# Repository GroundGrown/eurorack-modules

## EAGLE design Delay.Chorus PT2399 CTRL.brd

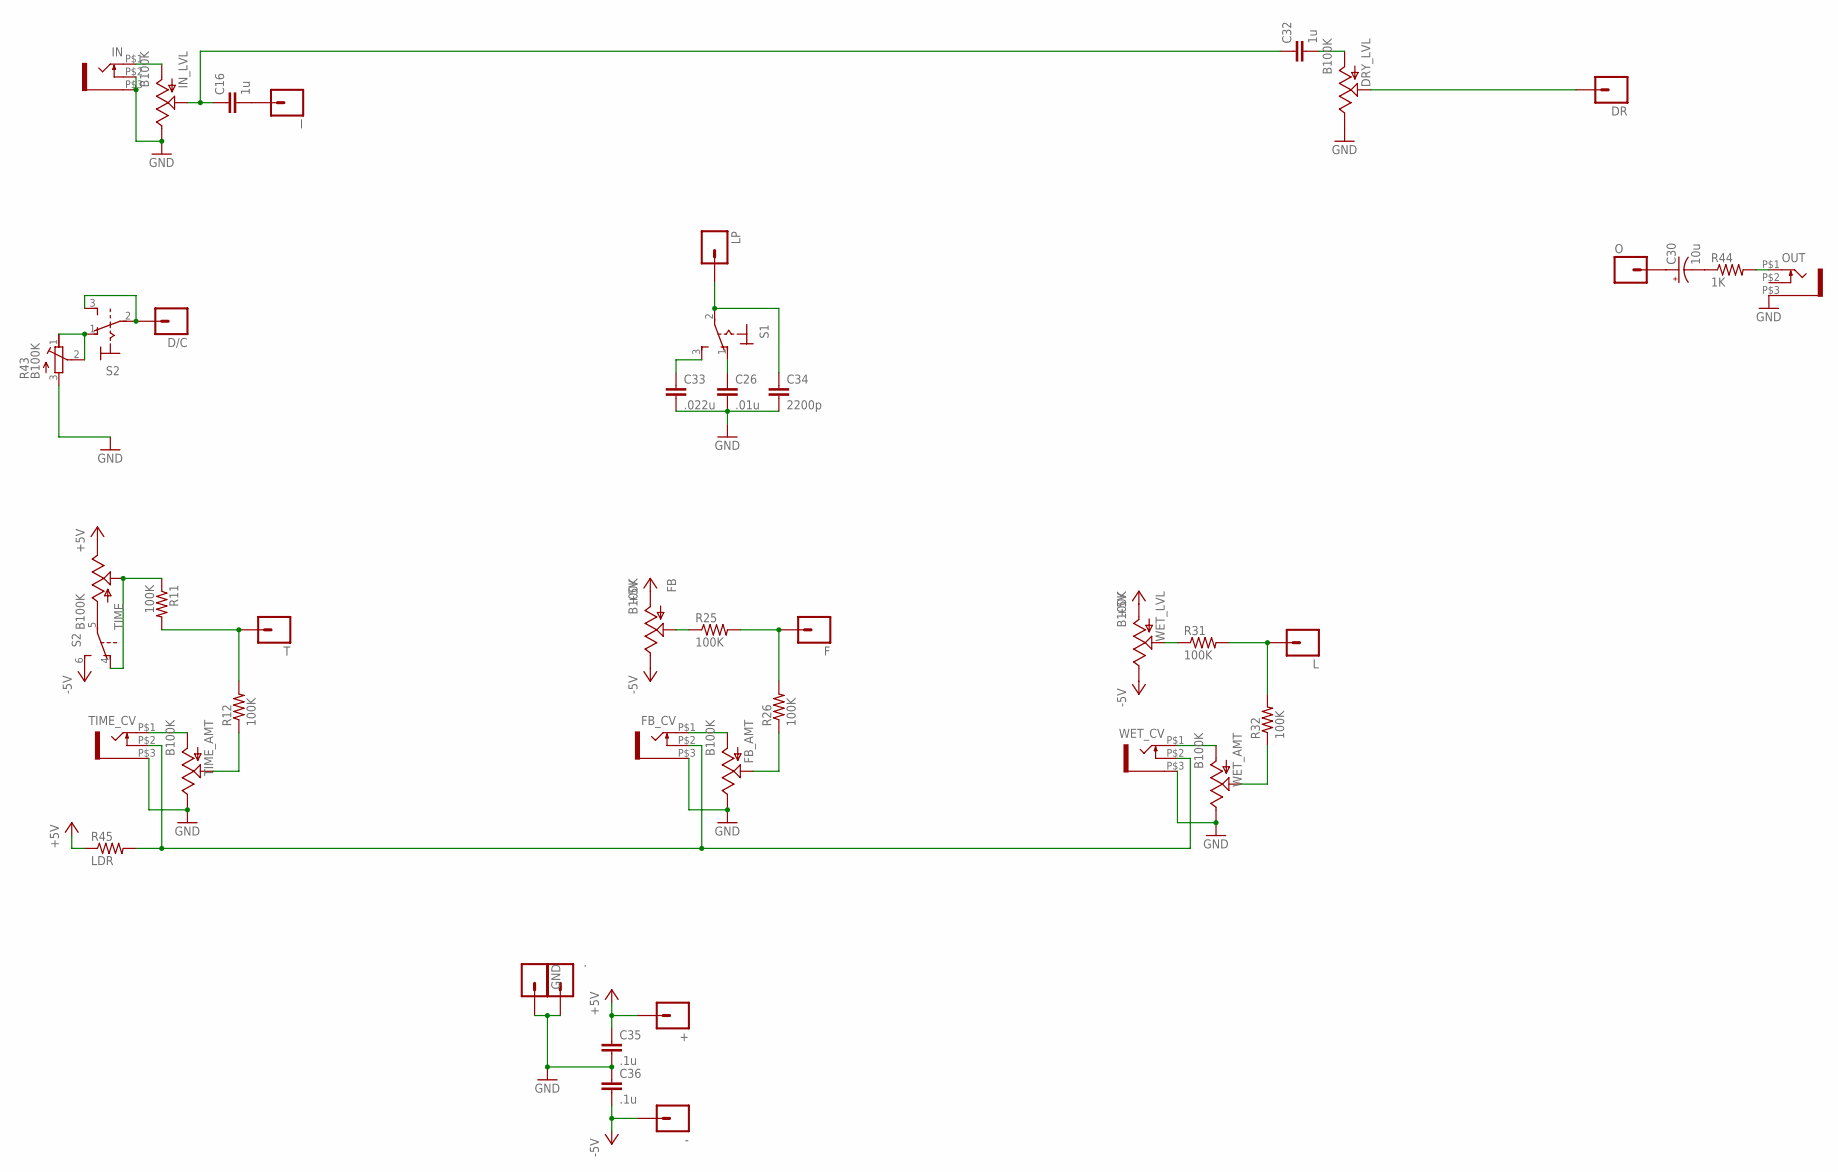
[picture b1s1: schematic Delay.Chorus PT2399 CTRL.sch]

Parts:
+: M01PTH; 1X01
-: M01PTH; 1X01
.: M01PTH; 1X01
C16, C32: 1u; 1206
C26: .01u; C5B2.5
C30: 10u; CPOL-RADIAL-10UF-25V
C33: .022u; C5B2.5
C34: 2200p; C5B2.5
C35, C36: .1u; 0805
D/C: M01PTH; 1X01
DR: M01PTH; 1X01
DRY_LVL: B100K; ALPS_POT
F: M01PTH; 1X01
FB: B100K; ALPS_POT
FB_AMT: B100K; ALPS_POT
FB_CV: WQP-PJ301M-12_JACK
GND: M01PTH; 1X01
I: M01PTH; 1X01
IN: WQP-PJ301M-12_JACK
IN_LVL: B100K; ALPS_POT
L: M01PTH; 1X01
LP: M01PTH; 1X01
O: M01PTH; 1X01
OUT: WQP-PJ301M-12_JACK
R11, R12, R25, R26, R31, R32: 100K; 0805
R43: B100K; RTRIM3314G
R44: 1K; 0805
R45: LDR; 1/6W-RES
S1: M9040P
S2: M9040P2
T: M01PTH; 1X01
TIME: B100K; ALPS_POT
TIME_AMT: B100K; ALPS_POT
TIME_CV: WQP-PJ301M-12_JACK
WET_AMT: B100K; ALPS_POT
WET_CV: WQP-PJ301M-12_JACK
WET_LVL: B100K; ALPS_POT

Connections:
+5V: +.1, C35.1, FB.P$3 (A), R45.1, TIME.P$1 (E), WET_LVL.P$3 (A)
-5V: -.1, C36.2, FB.P$1 (E), S2.6 (S), WET_LVL.P$1 (E)
GND: ..1, C26.2, C33.2, C34.2, C35.2, C36.1, DRY_LVL.P$1 (E), FB_AMT.P$1 (E), FB_CV.P$3 (1), GND.1, IN.P$2 (3), IN.P$3 (1), IN_LVL.P$1 (E), OUT.P$3 (1), R43.3 (A), TIME_AMT.P$1 (E), TIME_CV.P$3 (1), WET_AMT.P$1 (E), WET_CV.P$3 (1)
unnamed: D/C.1, S2.2, S2.3 (S)
unnamed: DR.1, DRY_LVL.P$2 (S)
unnamed: C30.1 (+), O.1
unnamed: S2.5, TIME.P$3 (A)
unnamed: C30.2 (-), R44.1
unnamed: OUT.P$1 (2), R44.2
unnamed: IN.P$1 (2), IN_LVL.P$3 (A)
unnamed: C16.1, C32.1, IN_LVL.P$2 (S)
unnamed: C16.2, I.1
unnamed: TIME_AMT.P$3 (A), TIME_CV.P$1 (2)
unnamed: R12.1, TIME_AMT.P$2 (S)
unnamed: R11.1, S2.4 (O), TIME.P$2 (S)
unnamed: R11.2, R12.2, T.1
unnamed: FB_AMT.P$3 (A), FB_CV.P$1 (2)
unnamed: FB_AMT.P$2 (S), R26.1
unnamed: FB.P$2 (S), R25.1
unnamed: F.1, R25.2, R26.2
unnamed: WET_AMT.P$3 (A), WET_CV.P$1 (2)
unnamed: R32.1, WET_AMT.P$2 (S)
unnamed: R31.1, WET_LVL.P$2 (S)
unnamed: L.1, R31.2, R32.2
unnamed: C32.2, DRY_LVL.P$3 (A)
unnamed: C26.1, S1.1 (O)
unnamed: C33.1, S1.3 (S)
unnamed: C34.1, LP.1, S1.2
unnamed: R43.1 (E), R43.2 (S), S2.1 (O)
unnamed: FB_CV.P$2 (3), R45.2, TIME_CV.P$2 (3), WET_CV.P$2 (3)

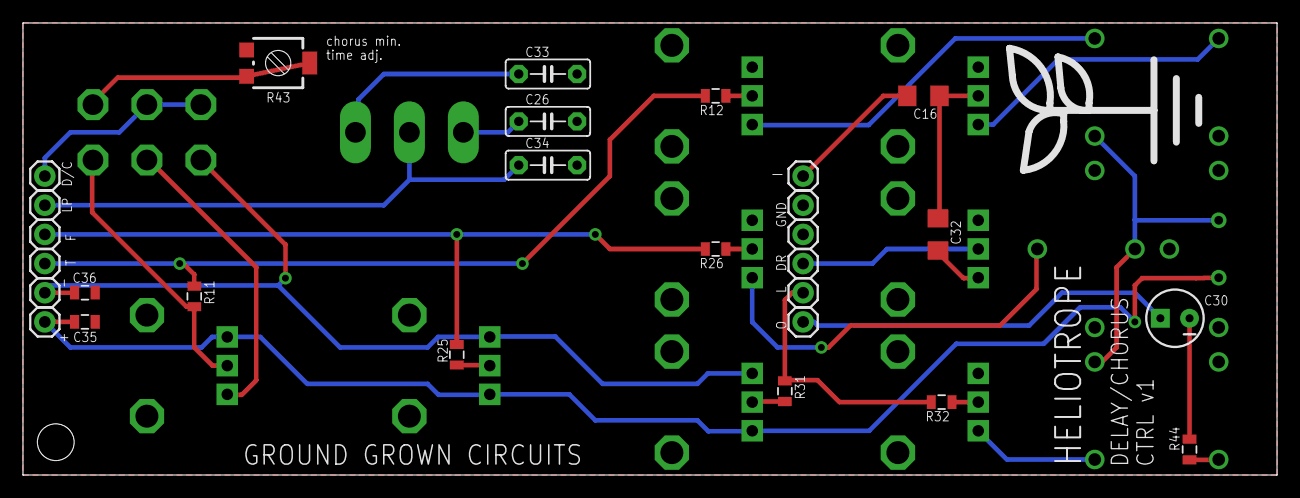
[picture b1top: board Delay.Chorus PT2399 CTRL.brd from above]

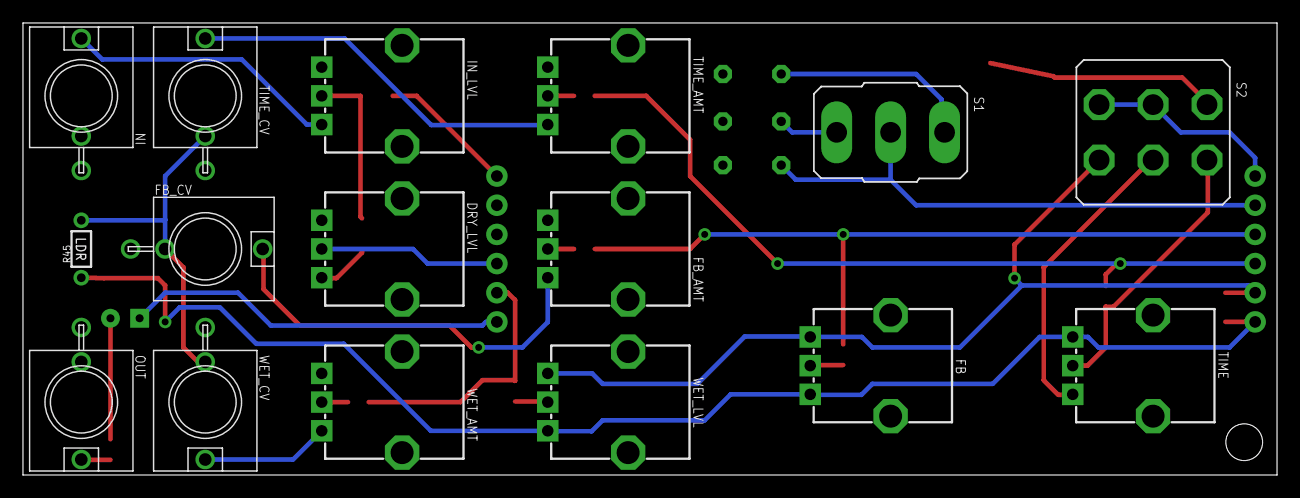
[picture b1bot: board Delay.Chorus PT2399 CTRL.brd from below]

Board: 2 copper layers, 109.2 x 39.4 mm, 45 parts (16 on the bottom side), 30 nets.

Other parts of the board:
U$1: LOGO_LARGE

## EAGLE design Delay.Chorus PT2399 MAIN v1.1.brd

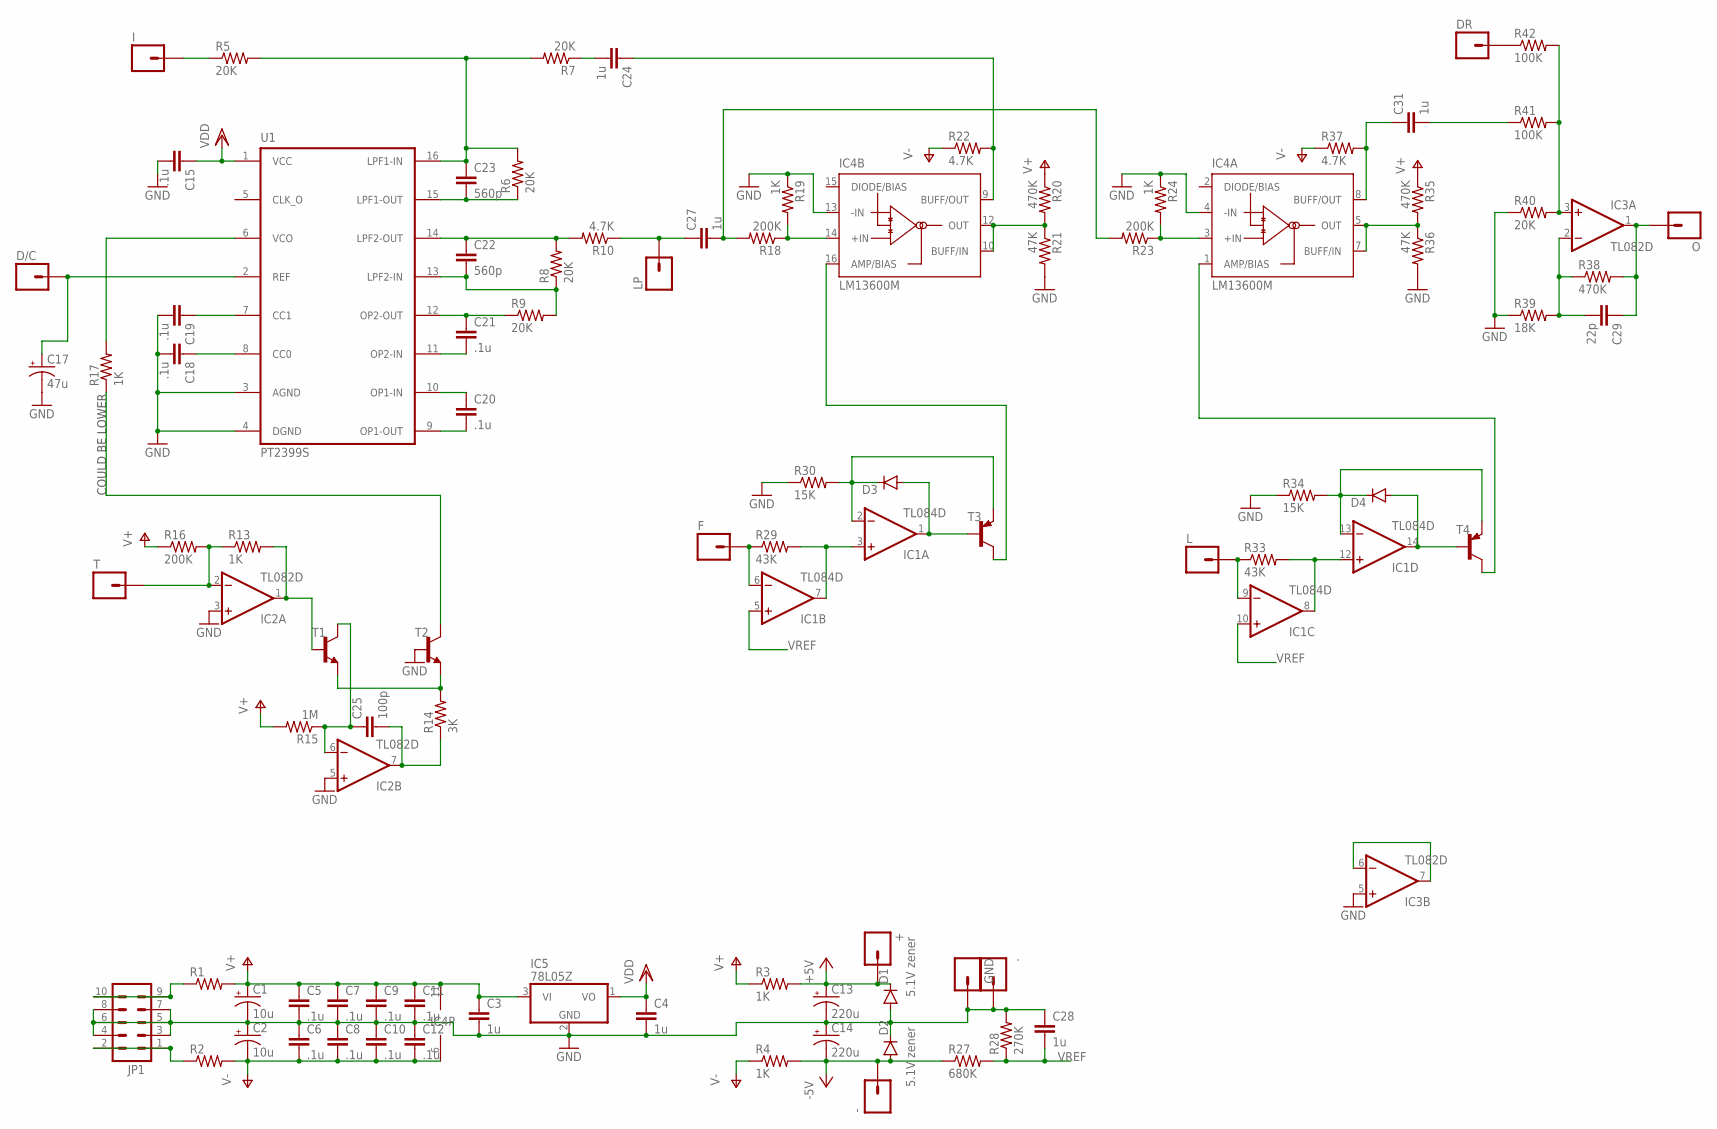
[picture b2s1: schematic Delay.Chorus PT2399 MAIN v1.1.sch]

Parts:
+: M01PTH; 1X01
-: M01PTH; 1X01
.: M01PTH; 1X01
C1, C2: 10u; CPOL-RADIAL-10UF-25V
C3, C4, C24, C27, C28, C31: 1u; 0805
C5, C6, C7, C8, C9, C10, C11, C12, C15, C18, C19, C20, C21: .1u; 0805
C13, C14: 220u; E2,5-5
C17: 47u; E2,5-5
C22, C23: 560p; 0805
C25: 100p; 0805
C29: 22p; 0805
D1, D2: 5.1V zener; SOD-123
D3, D4: DIODESOD123; SOD-123
D/C: M01PTH; 1X01
DR: M01PTH; 1X01
F: M01PTH; 1X01
GND: M01PTH; 1X01
I: M01PTH; 1X01
IC1: TL084D; SO14
IC2, IC3: TL082D; SO08
IC4: LM13600M; SO16
IC5: 78L05Z; TO92
JP1: M05X2PTH; AVR_ICSP
L: M01PTH; 1X01
LP: M01PTH; 1X01
O: M01PTH; 1X01
R1, R2: RESISTOR0805-RES; 0805
R3, R4, R13, R17, R19, R24: 1K; 0805
R5, R6, R7, R8, R9, R40: 20K; 0805
R10, R22, R37: 4.7K; 0805
R14: 3K; 0805
R15: 1M; 0805
R16, R18, R23: 200K; 0805
R20, R35, R38: 470K; 0805
R21, R36: 47K; 0805
R27: 680K; 0805
R28: 270K; 0805
R29, R33: 43K; 0805
R30, R34: 15K; 0805
R39: 18K; 0805
R41, R42: 100K; 0805
T: M01PTH; 1X01
T1, T2: MMBT3904LT1-NPN-SOT23-BEC; SOT23-BEC
T3, T4: MMBT3906LT1-PNP-SOT23-BEC; SOT23-BEC
U1: PT2399S; SO16W

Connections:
+5V: +.1, C13.+, D1.C, R3.2
-5V: -.1, C14.-, D2.A, R4.2, R27.1
GND: ..1, C1.2 (-), C2.1 (+), C3.2, C4.2, C5.2, C6.1, C7.2, C8.1, C9.2, C10.1, C11.2, C12.1, C13.-, C14.+, C15.2, C17.-, C18.2, C19.2, C28.1, D1.A, D2.C, GND.1, IC2.3 (+IN), IC2.5 (+IN), IC3.5 (+IN), IC4.4 (-IN), IC4.13 (-IN), IC5.2 (GND), JP1.3, JP1.4, JP1.5, JP1.6, JP1.7, JP1.8, R19.1, R21.2, R24.1, R28.2, R30.1, R34.1, R36.2, R39.1, R40.1, T2.B, U1.3 (AGND), U1.4 (DGND)
unnamed: C17.+, D/C.1, U1.2 (REF)
unnamed: C19.1, U1.7 (CC1)
unnamed: C18.1, U1.8 (CC0)
unnamed: C23.1, R5.2, R6.2, R7.2, U1.16 (LPF1-IN)
unnamed: C22.1, R8.2, R10.2, U1.14 (LPF2-OUT)
unnamed: C22.2, R8.1, R9.2, U1.13 (LPF2-IN)
unnamed: C21.1, R9.1, U1.12 (OP2-OUT)
unnamed: C21.2, U1.11 (OP2-IN)
unnamed: JP1.1, JP1.2, R2.1
unnamed: JP1.9, JP1.10, R1.1
unnamed: C20.1, U1.10 (OP1-IN)
unnamed: C20.2, U1.9 (OP1-OUT)
unnamed: C23.2, R6.1, U1.15 (LPF1-OUT)
unnamed: DR.1, R42.1
unnamed: I.1, R5.1
unnamed: C24.2, R7.1
unnamed: C24.1, IC4.9 (BUFF/OUT), R22.2
unnamed: F.1, IC1.6 (-IN), R29.1
unnamed: IC2.2 (-IN), R13.1, R16.2, T.1
unnamed: IC2.1 (OUT), R13.2, T1.B
unnamed: R14.2, T1.E, T2.E
unnamed: C25.2, IC2.7 (OUT), R14.1
unnamed: C25.1, IC2.6 (-IN), R15.1, T1.C
unnamed: C27.2, R18.2, R23.2
unnamed: R17.1, T2.C
unnamed: R17.2, U1.6 (VCO)
unnamed: IC4.14 (+IN), R18.1, R19.2
unnamed: IC4.10 (BUFF/IN), IC4.12 (OUT), R20.2, R21.1
unnamed: IC4.3 (+IN), R23.1, R24.2
unnamed: IC1.3 (+IN), IC1.7 (OUT), R29.2
unnamed: D3.C, IC1.2 (-IN), R30.2, T3.E
unnamed: D3.A, IC1.1 (OUT), T3.B
unnamed: IC4.5 (OUT), IC4.7 (BUFF/IN), R35.2, R36.1
unnamed: IC4.16 (AMP/BIAS), T3.C
unnamed: IC1.8 (OUT), IC1.12 (+IN), R33.2
unnamed: D4.C, IC1.13 (-IN), R34.2, T4.E
unnamed: D4.A, IC1.14 (OUT), T4.B
unnamed: IC4.1 (AMP/BIAS), T4.C
unnamed: C31.1, IC4.8 (BUFF/OUT), R37.2
unnamed: C29.2, IC3.2 (-IN), R38.1, R39.2
unnamed: C29.1, IC3.1 (OUT), O.1, R38.2
unnamed: IC1.9 (-IN), L.1, R33.1
unnamed: IC3.3 (+IN), R40.2, R41.2, R42.2
unnamed: C31.2, R41.1
unnamed: IC3.6 (-IN), IC3.7 (OUT)
unnamed: C27.1, LP.1, R10.1
V+: C1.1 (+), C3.1, C5.1, C7.1, C9.1, C11.1, IC1.4 (V+), IC2.8 (V+), IC3.8 (V+), IC4.11 (V+), IC5.3 (VI), R1.2, R3.1, R15.2, R16.1, R20.1, R35.1
V-: C2.2 (-), C6.2, C8.2, C10.2, C12.2, IC1.11 (V-), IC2.4 (V-), IC3.4 (V-), IC4.6 (V-), R2.2, R4.1, R22.1, R37.1
VDD: C4.1, C15.1, IC5.1 (VO), U1.1 (VCC)
VREF: C28.2, IC1.5 (+IN), IC1.10 (+IN), R27.2, R28.1

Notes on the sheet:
COULD BE LOWER

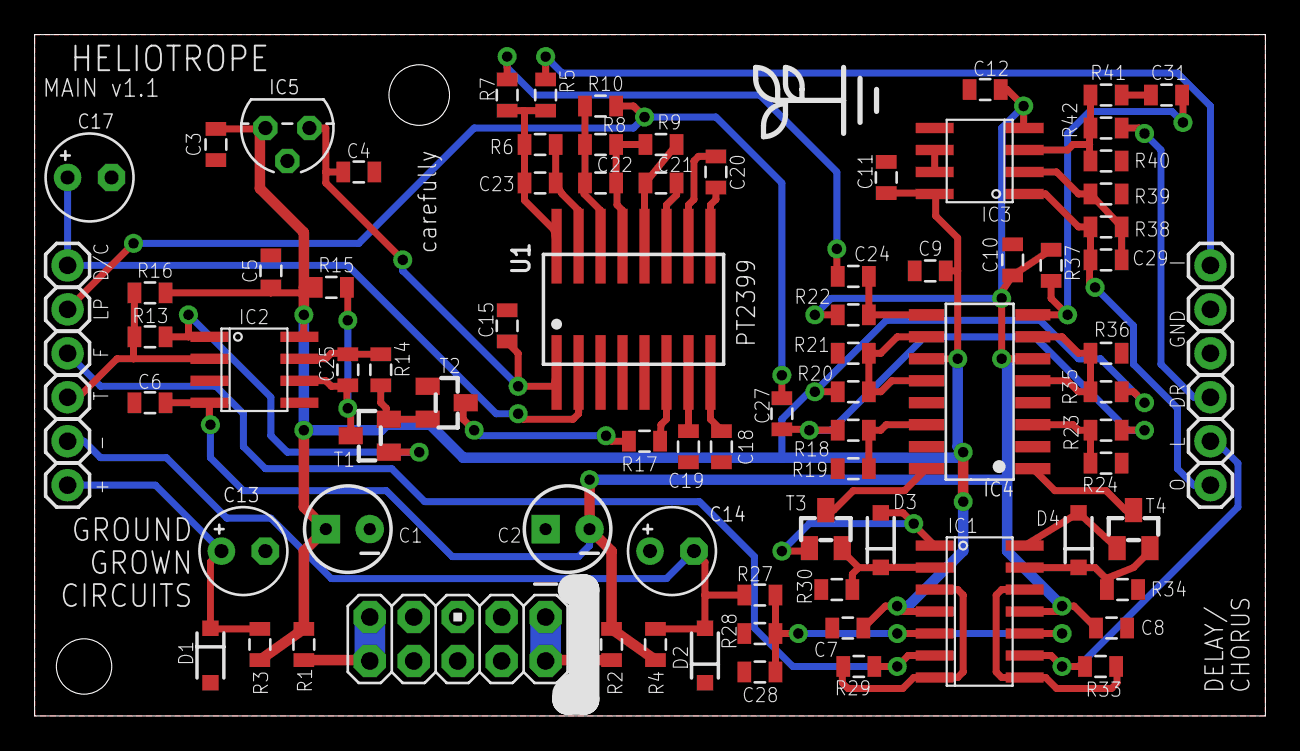
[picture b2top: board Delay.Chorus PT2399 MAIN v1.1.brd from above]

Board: 2 copper layers, 71.1 x 39.4 mm, 92 parts (0 on the bottom side), 53 nets.

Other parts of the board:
U$1: LOGO_SMALL

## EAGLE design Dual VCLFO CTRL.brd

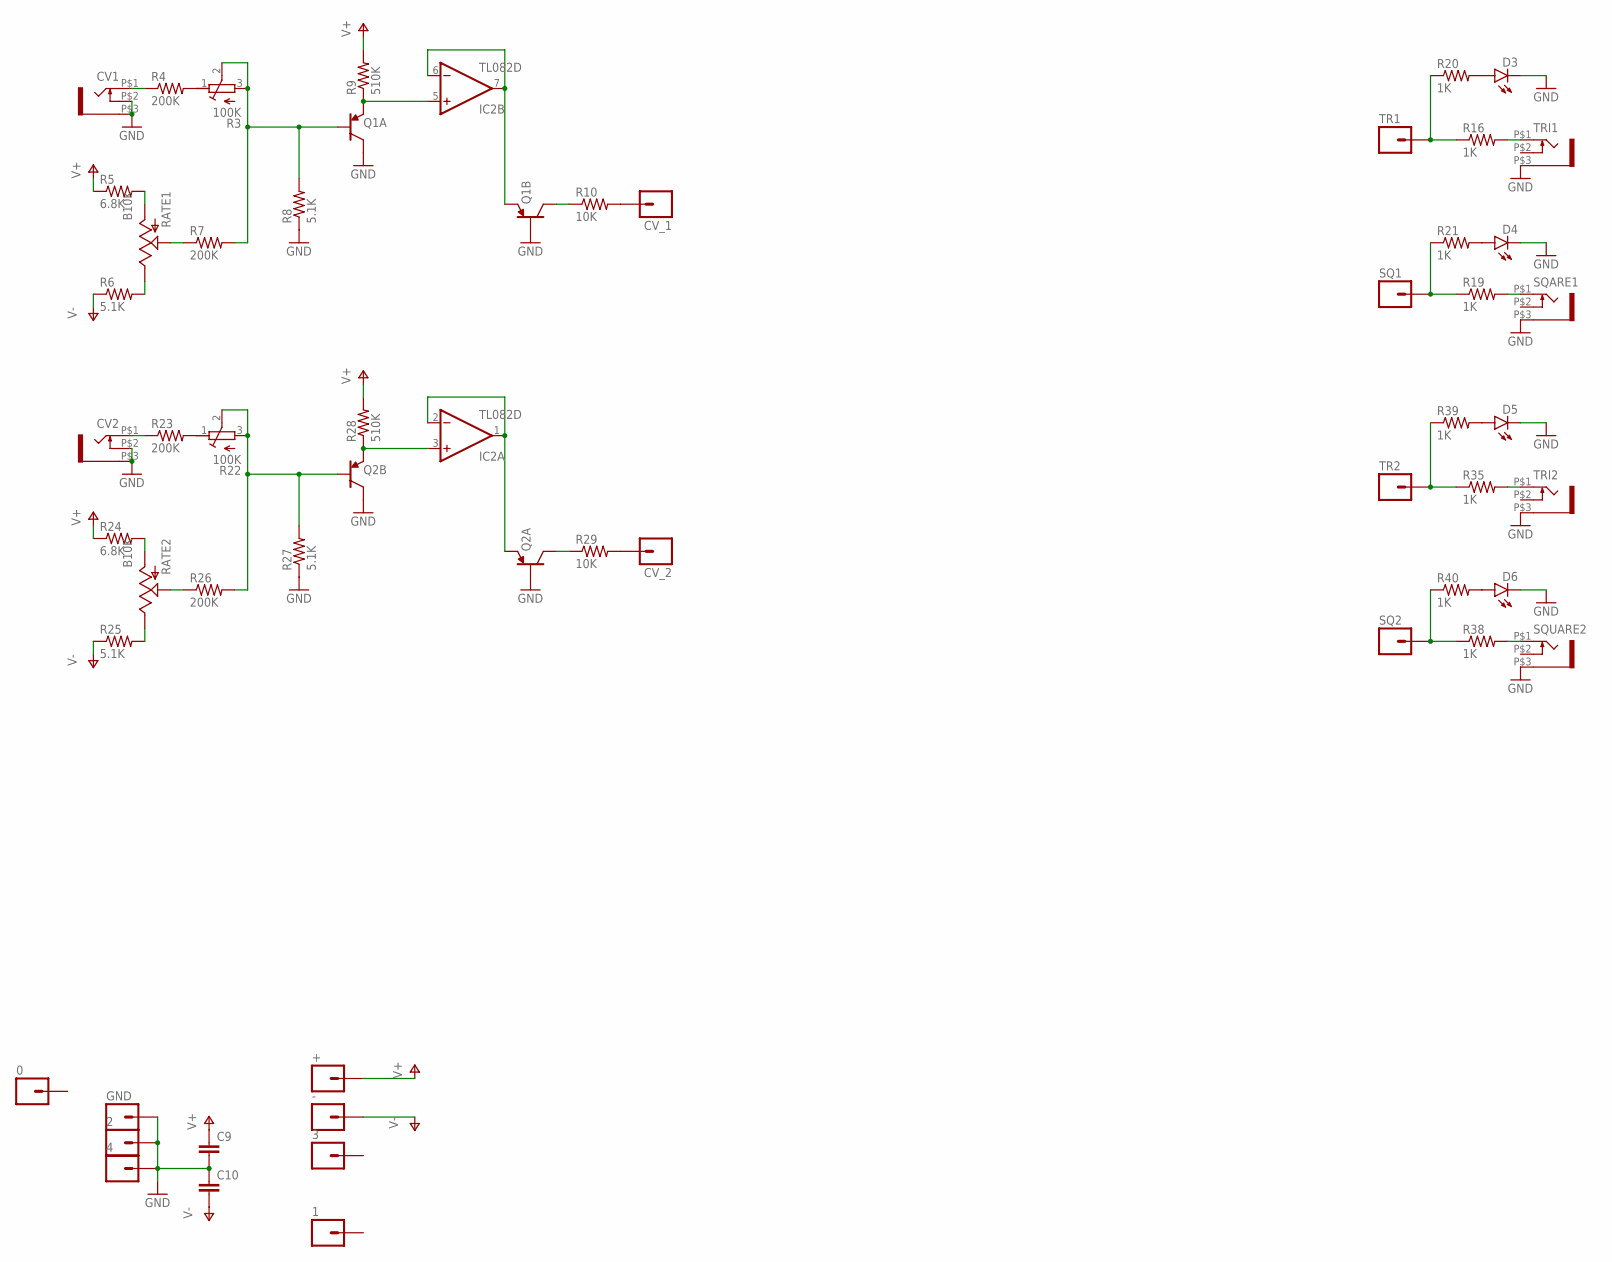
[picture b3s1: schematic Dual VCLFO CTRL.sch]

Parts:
0, 1, 2, 3, 4: M01PTH; 1X01
+: M01PTH; 1X01
-: M01PTH; 1X01
C9, C10: CAP0805; 0805
CV1, CV2: WQP-PJ301M-12_JACK
CV_1, CV_2: M01PTH; 1X01
D3, D4, D5, D6: LED3MM
GND: M01PTH; 1X01
IC2: TL082D; SO08
Q1, Q2: PNP-DUALPMP5201; SOT363
R3, R22: 100K; RTRIM3314G
R4, R7, R23, R26: 200K; 0805
R5, R24: 6.8K; 0805
R6, R8, R25, R27: 5.1K; 0805
R9, R28: 510K; 0805
R10, R29: 10K; 0805
R16, R19, R20, R21, R35, R38, R39, R40: 1K; 0805
RATE1, RATE2: B10K; ALPS_POT
SQ1, SQ2: M01PTH; 1X01
SQARE1: WQP-PJ301M-12_JACK
SQUARE2: WQP-PJ301M-12_JACK
TR1, TR2: M01PTH; 1X01
TRI1, TRI2: WQP-PJ301M-12_JACK

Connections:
GND: 2.1, 4.1, C9.2, C10.1, CV1.P$2 (3), CV1.P$3 (1), CV2.P$2 (3), CV2.P$3 (1), D3.K (C), D4.K (C), D5.K (C), D6.K (C), GND.1, Q1.P$2, Q1.P$6, Q2.P$1, Q2.P$3, R8.1, R27.1, SQARE1.P$3 (1), SQUARE2.P$3 (1), TRI1.P$3 (1), TRI2.P$3 (1)
unnamed: Q1.P$1, R3.2 (S), R3.3 (A), R7.2, R8.2
unnamed: IC2.5 (+IN), Q1.P$5, R9.1
unnamed: Q2.P$2, R22.2 (S), R22.3 (A), R26.2, R27.2
unnamed: CV_1.1, R10.2
unnamed: CV_2.1, R29.2
unnamed: IC2.6 (-IN), IC2.7 (OUT), Q1.P$4
unnamed: Q1.P$3, R10.1
unnamed: R3.1 (E), R4.2
unnamed: CV1.P$1 (2), R4.1
unnamed: R5.2, RATE1.P$3 (A)
unnamed: R6.2, RATE1.P$1 (E)
unnamed: R7.1, RATE1.P$2 (S)
unnamed: R19.1, R21.1, SQ1.1
unnamed: R16.1, R20.1, TR1.1
unnamed: R22.1 (E), R23.2
unnamed: R16.2, TRI1.P$1 (2)
unnamed: R19.2, SQARE1.P$1 (2)
unnamed: D3.A, R20.2
unnamed: D4.A, R21.2
unnamed: CV2.P$1 (2), R23.1
unnamed: R24.2, RATE2.P$3 (A)
unnamed: R25.2, RATE2.P$1 (E)
unnamed: R26.1, RATE2.P$2 (S)
unnamed: IC2.3 (+IN), Q2.P$4, R28.1
unnamed: IC2.1 (OUT), IC2.2 (-IN), Q2.P$5
unnamed: Q2.P$6, R29.1
unnamed: R38.1, R40.1, SQ2.1
unnamed: R35.1, R39.1, TR2.1
unnamed: R35.2, TRI2.P$1 (2)
unnamed: R38.2, SQUARE2.P$1 (2)
unnamed: D5.A, R39.2
unnamed: D6.A, R40.2
V+: +.1, C9.1, IC2.8 (V+), R5.1, R9.2, R24.1, R28.2
V-: -.1, C10.2, IC2.4 (V-), R6.1, R25.1

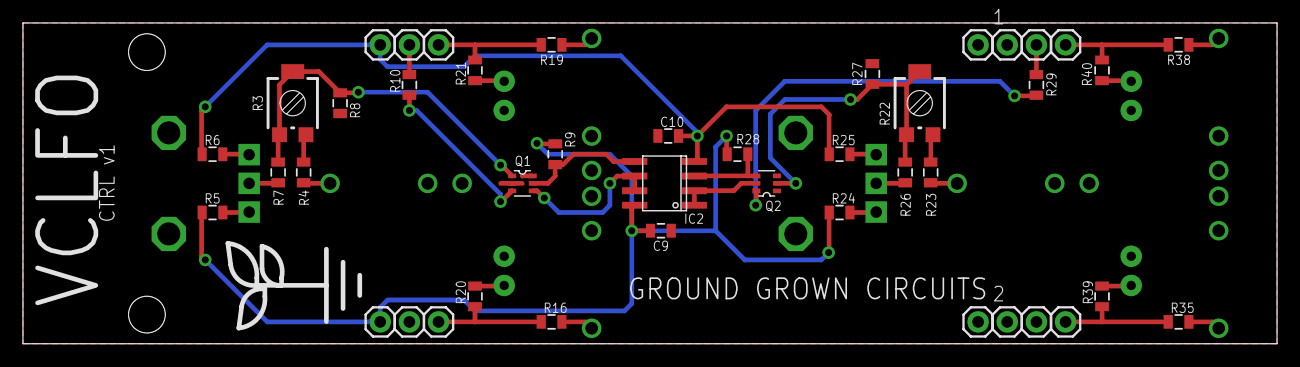
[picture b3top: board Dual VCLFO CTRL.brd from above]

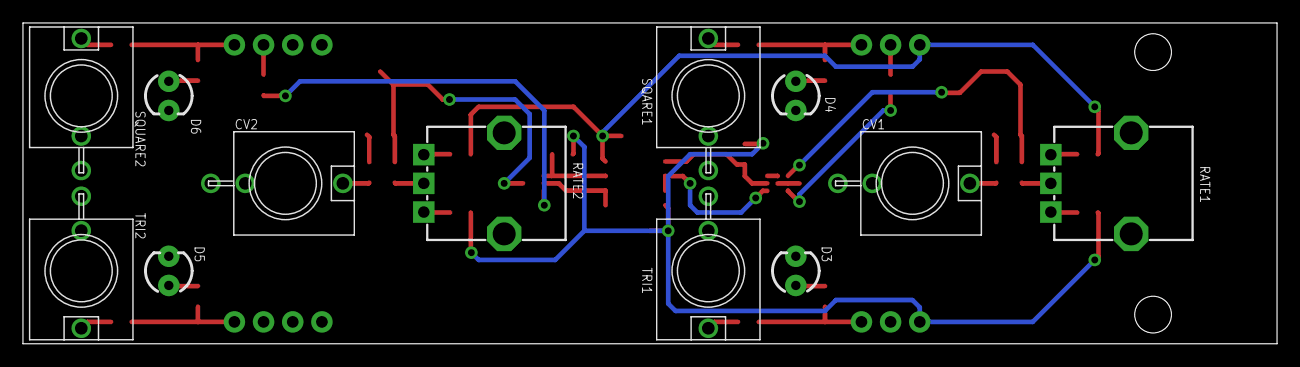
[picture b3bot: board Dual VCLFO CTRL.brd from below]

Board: 2 copper layers, 109.2 x 27.9 mm, 56 parts (12 on the bottom side), 35 nets.

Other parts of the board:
U$1: LOGO_MED

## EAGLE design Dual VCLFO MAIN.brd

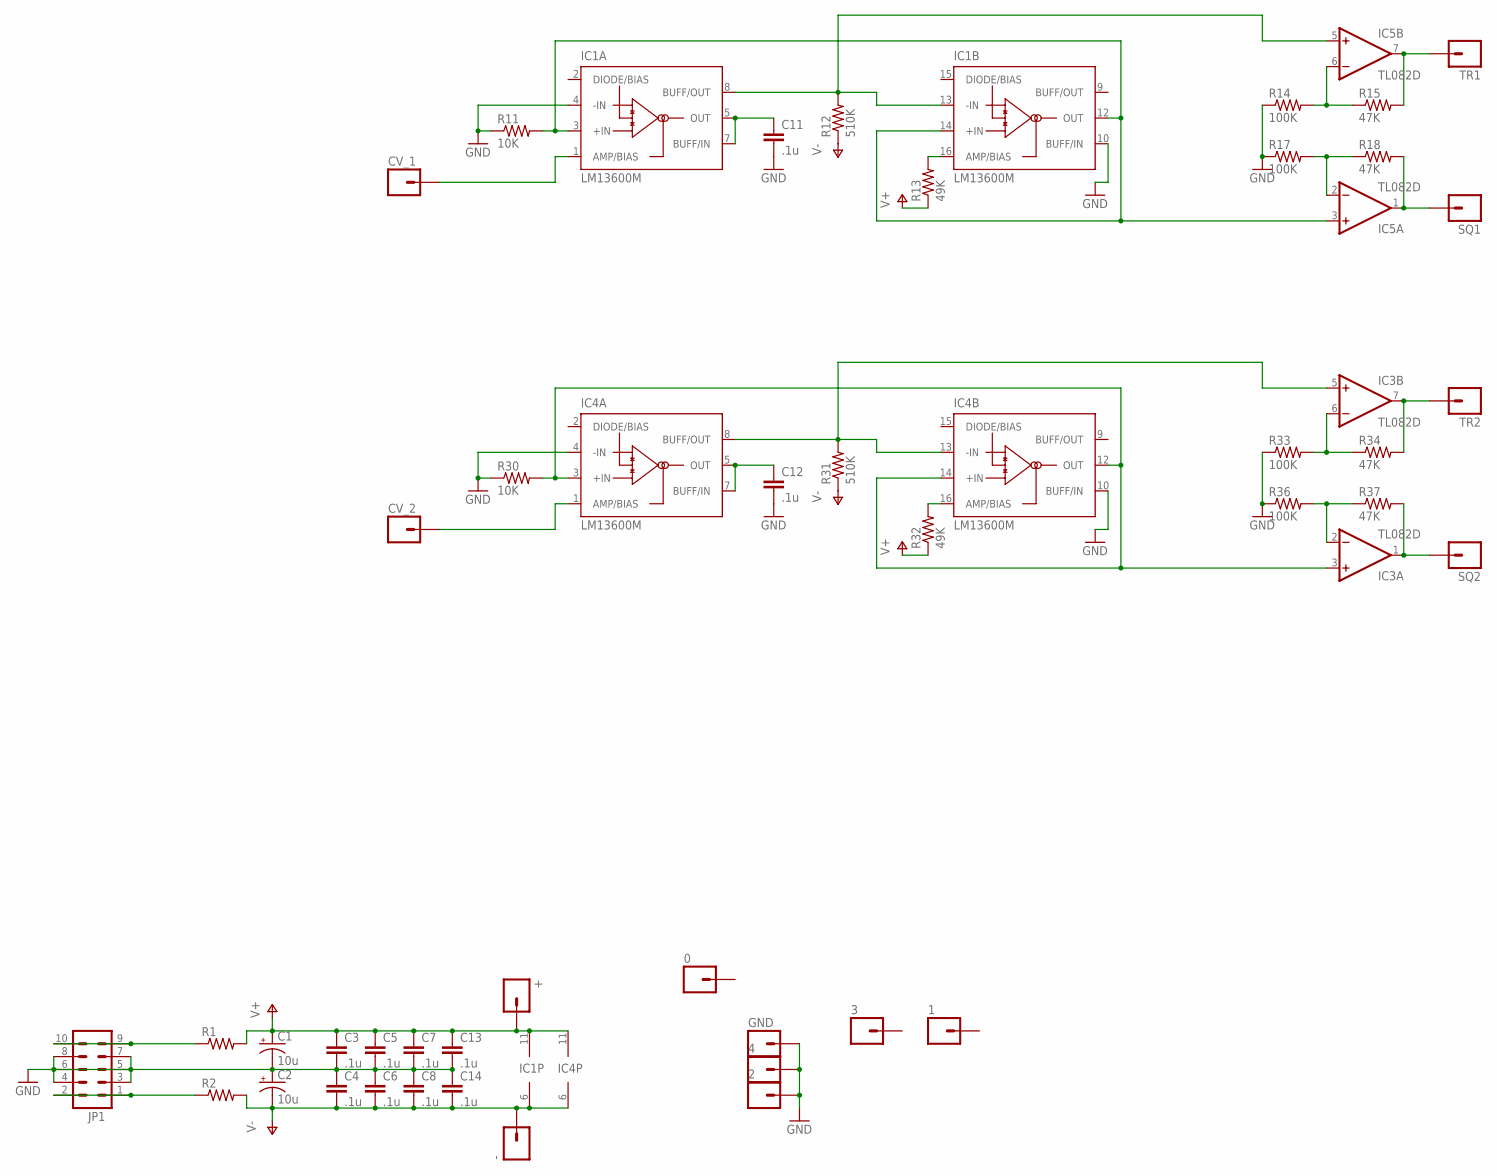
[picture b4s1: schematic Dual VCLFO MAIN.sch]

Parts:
0, 1, 2, 3, 4: M01PTH; 1X01
+: M01PTH; 1X01
-: M01PTH; 1X01
C1, C2: 10u; CPOL-RADIAL-10UF-25V
C3, C4, C5, C6, C7, C8, C13, C14: .1u; 0805
C11, C12: .1u; CAP-PTH-5MM
CV_1, CV_2: M01PTH; 1X01
GND: M01PTH; 1X01
IC1, IC4: LM13600M; SO16
IC3, IC5: TL082D; SO08
JP1: M05X2PTH; AVR_ICSP
R1, R2: RESISTOR0805-RES; 0805
R11, R30: 10K; 0805
R12, R31: 510K; 0805
R13, R32: 49K; 0805
R14, R17, R33, R36: 100K; 0805
R15, R18, R34, R37: 47K; 0805
SQ1, SQ2: M01PTH; 1X01
TR1, TR2: M01PTH; 1X01

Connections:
GND: 2.1, 4.1, C1.2 (-), C2.1 (+), C3.2, C4.1, C5.2, C6.1, C7.2, C8.1, C11.2, C12.2, C13.2, C14.1, GND.1, IC1.4 (-IN), IC1.10 (BUFF/IN), IC4.4 (-IN), IC4.10 (BUFF/IN), JP1.3, JP1.4, JP1.5, JP1.6, JP1.7, JP1.8, R11.1, R14.1, R17.1, R30.1, R33.1, R36.1
unnamed: JP1.9, JP1.10, R1.1
unnamed: JP1.1, JP1.2, R2.1
unnamed: IC5.2 (-IN), R17.2, R18.1
unnamed: IC3.1 (OUT), R37.2, SQ2.1
unnamed: C11.1, IC1.5 (OUT), IC1.7 (BUFF/IN)
unnamed: IC1.8 (BUFF/OUT), IC1.13 (-IN), IC5.5 (+IN), R12.2
unnamed: IC1.3 (+IN), IC1.12 (OUT), IC1.14 (+IN), IC5.3 (+IN), R11.2
unnamed: IC1.16 (AMP/BIAS), R13.2
unnamed: CV_1.1, IC1.1 (AMP/BIAS)
unnamed: IC5.1 (OUT), R18.2, SQ1.1
unnamed: IC5.6 (-IN), R14.2, R15.1
unnamed: IC5.7 (OUT), R15.2, TR1.1
unnamed: C12.1, IC4.5 (OUT), IC4.7 (BUFF/IN)
unnamed: IC3.5 (+IN), IC4.8 (BUFF/OUT), IC4.13 (-IN), R31.2
unnamed: IC3.3 (+IN), IC4.3 (+IN), IC4.12 (OUT), IC4.14 (+IN), R30.2
unnamed: IC4.16 (AMP/BIAS), R32.2
unnamed: CV_2.1, IC4.1 (AMP/BIAS)
unnamed: IC3.2 (-IN), R36.2, R37.1
unnamed: IC3.6 (-IN), R33.2, R34.1
unnamed: IC3.7 (OUT), R34.2, TR2.1
V+: +.1, C1.1 (+), C3.1, C5.1, C7.1, C13.1, IC1.11 (V+), IC3.8 (V+), IC4.11 (V+), IC5.8 (V+), R1.2, R13.1, R32.1
V-: -.1, C2.2 (-), C4.2, C6.2, C8.2, C14.2, IC1.6 (V-), IC3.4 (V-), IC4.6 (V-), IC5.4 (V-), R2.2, R12.1, R31.1

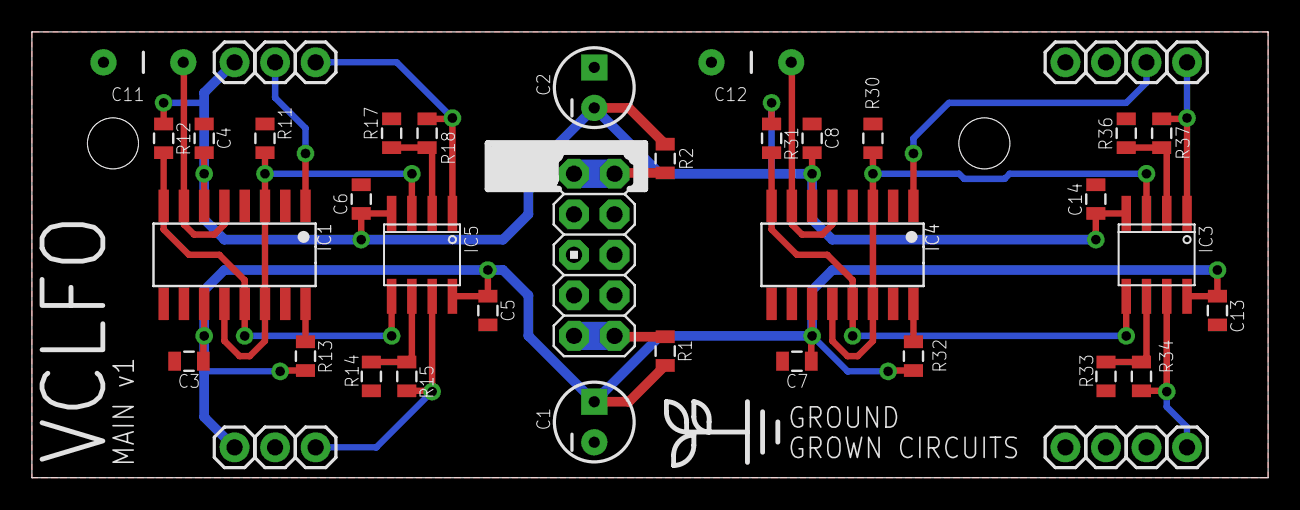
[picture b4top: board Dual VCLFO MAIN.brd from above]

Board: 2 copper layers, 77.5 x 27.9 mm, 48 parts (0 on the bottom side), 23 nets.

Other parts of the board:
U$1: LOGO_SMALL

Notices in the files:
parts and their libraries:
SparkFun-Capacitors: Licensing: Creative Commons ShareAlike 4.0 International - https://creativecommons.org/licenses/by-sa/4.0
princeton-tech: Copyright (C) 2010, Bob Starr
